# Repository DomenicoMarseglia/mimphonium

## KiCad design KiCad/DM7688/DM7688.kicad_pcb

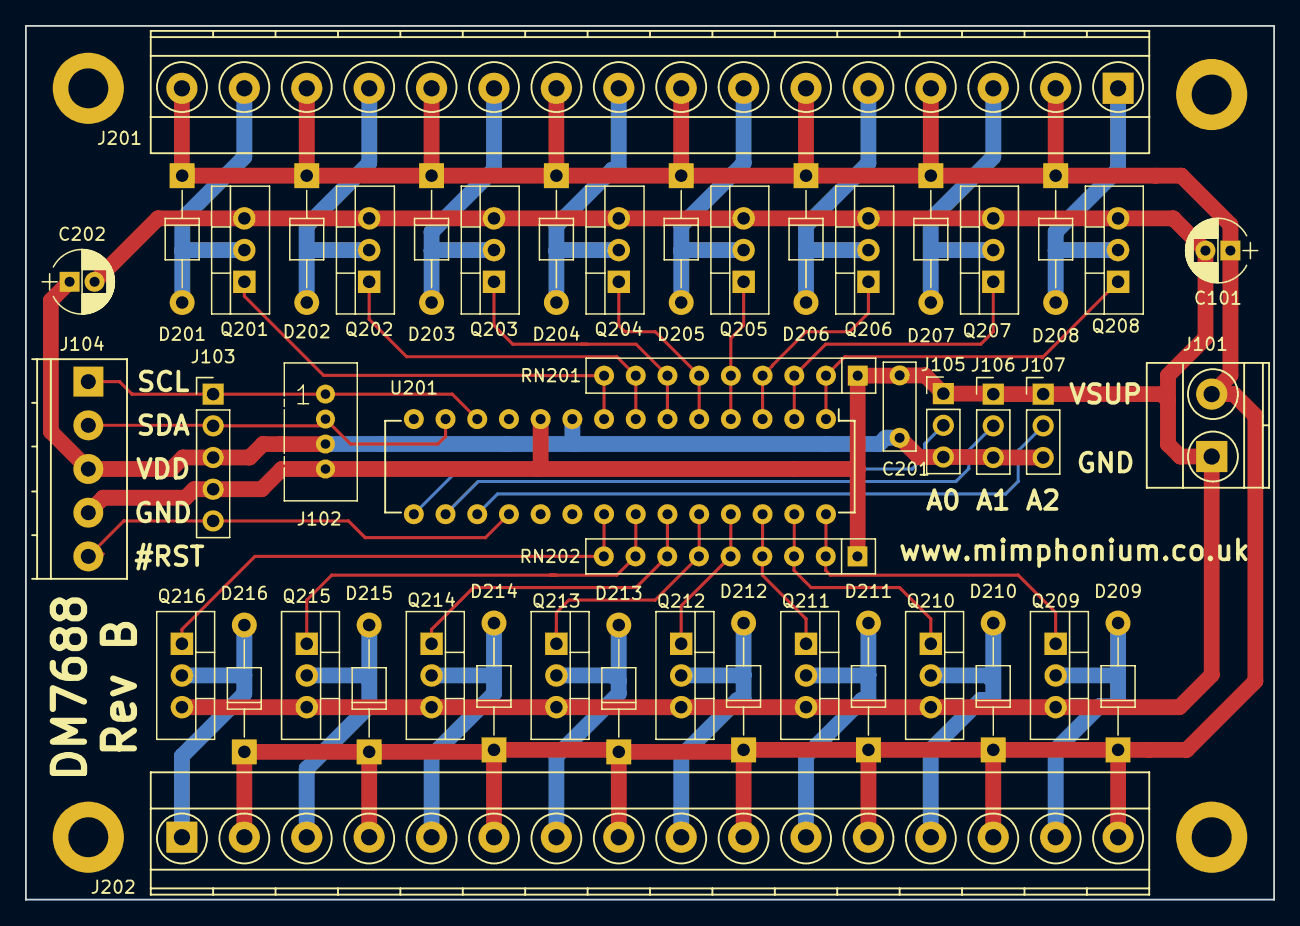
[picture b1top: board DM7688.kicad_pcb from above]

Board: 2 copper layers, 100.0 x 70.0 mm, 51 parts (0 on the bottom side), 41 nets.

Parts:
C101, C202: 10uF; CP_Radial_D5.0mm_P2.00mm
C201: 100nF; C_Disc_D7.0mm_W2.5mm_P5.00mm
D201, D202, D203, D204, D205, D206, D207, D208, D209, D210, D211, D212, D213, D214, D215, D216: 1N4001; D_T-1_P10.16mm_Horizontal
J101: Screw_Terminal_01x02; TerminalBlock_Pheonix_MKDS1.5-2pol
J102: Conn_01x04; Grove_1x04
J103: Conn_01x05; Pin_Header_Straight_1x05_Pitch2.54mm
J104: Screw_Terminal_01x05; TerminalBlock_Pheonix_PT-3.5mm_5pol
J105, J106, J107: Conn_01x03; Pin_Header_Straight_1x03_Pitch2.54mm
J108, J109, J110, J111: Conn_01x01; MountingHole_3.2mm_M3_ISO7380_Pad
J201, J202: Screw_Terminal_01x16; TerminalBlock_Pheonix_MKDS1.5-16pol
Q201, Q202, Q203, Q204, Q205, Q206, Q207, Q208, Q209, Q210, Q211, Q212, Q213, Q214, Q215, Q216: IRF540N; TO-220_Vertical
RN201, RN202: R_Network08; R_Array_SIP9
U201: MCP23017; DIP-28_W7.62mm

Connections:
/Output1-16/#RESET: J103.5, J104.5, U201.18
/Output1-16/A0: J105.2, U201.15
/Output1-16/A1: J106.2, U201.16
/Output1-16/A2: J107.2, U201.17
/Output1-16/SCL: J102.1, J103.1, J104.1, U201.12
/Output1-16/SDA: J102.2, J103.2, J104.2, U201.13
/Output1-16/VCoilA: C101.1, D201.1, D202.1, D203.1, D204.1, D205.1, D206.1, D207.1, D208.1, D209.1, D210.1, D211.1, D212.1, D213.1, D214.1, D215.1, D216.1, J101.2, J201.2, J201.4, J201.6, J201.8, J201.10, J201.12, J201.14, J201.16, J202.2, J202.4, J202.6, J202.8, J202.10, J202.12, J202.14, J202.16
GNDPWR: C101.2, C201.2, C202.2, J101.1, J102.4, J103.4, J104.4, J105.1, J106.1, J107.1, Q201.3, Q202.3, Q203.3, Q204.3, Q205.3, Q206.3, Q207.3, Q208.3, Q209.3, Q210.3, Q211.3, Q212.3, Q213.3, Q214.3, Q215.3, Q216.3, RN201.1, RN202.1, U201.10
unnamed: D201.2, J201.15, Q201.2
unnamed: D202.2, J201.13, Q202.2
unnamed: D203.2, J201.11, Q203.2
unnamed: D204.2, J201.9, Q204.2
unnamed: D205.2, J201.7, Q205.2
unnamed: D206.2, J201.5, Q206.2
unnamed: D207.2, J201.3, Q207.2
unnamed: D208.2, J201.1, Q208.2
unnamed: D209.2, J202.15, Q209.2
unnamed: D210.2, J202.13, Q210.2
unnamed: D211.2, J202.11, Q211.2
unnamed: D212.2, J202.9, Q212.2
unnamed: D213.2, J202.7, Q213.2
unnamed: D214.2, J202.5, Q214.2
unnamed: D215.2, J202.3, Q215.2
unnamed: D216.2, J202.1, Q216.2
unnamed: Q201.1, RN201.9, U201.8
unnamed: Q202.1, RN201.8, U201.7
unnamed: Q203.1, RN201.7, U201.6
unnamed: Q204.1, RN201.6, U201.5
unnamed: Q205.1, RN201.5, U201.4
unnamed: Q206.1, RN201.4, U201.3
unnamed: Q207.1, RN201.3, U201.2
unnamed: Q208.1, RN201.2, U201.1
unnamed: Q209.1, RN202.2, U201.28
unnamed: Q210.1, RN202.3, U201.27
unnamed: Q211.1, RN202.4, U201.26
unnamed: Q212.1, RN202.5, U201.25
unnamed: Q213.1, RN202.6, U201.24
unnamed: Q214.1, RN202.7, U201.23
unnamed: Q215.1, RN202.8, U201.22
unnamed: Q216.1, RN202.9, U201.21
VCC: C201.1, C202.1, J102.3, J103.3, J104.3, J105.3, J106.3, J107.3, U201.9

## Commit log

2020-01-30 Actually add the .scad files
2020-01-30 Added KiCad files for DM7688 board
2020-02-08 Added mimphonium Arduino source code
2020-02-08 Added MidiToSrc application
2020-02-08 Added sample midi files
2020-02-08 Added missing file from midifile library
